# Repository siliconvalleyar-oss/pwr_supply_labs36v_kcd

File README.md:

# Fuente de Laboratorio Analógica 0-36V DC

Proyecto KiCad de una fuente de alimentación de laboratorio regulada, de 0 a 36 voltios DC, con diseño 100% analógico.

## Especificaciones

| Parámetro | Valor |
|-----------|-------|
| Salida | 0 – 36 V DC continuo |
| Corriente máxima | 5 A |
| Topología | Lineal, regulador serie |
| Control | Analógico (BJT + MOSFET) |
| Indicador | LED de potencia |
| Tensión de entrada | A definir (transformador + rectificador) |

## Estructura del Proyecto

```
pwr_supply_labs36v_kcd/
├── power_supply_36v_analog/
│   ├── power_supply_36v_analog.kicad_pro    # Archivo principal KiCad
│   ├── power_supply_36v.kicad_sch           # Esquema raíz (jerárquico)
│   ├── control_driver.kicad_sch             # Hoja: driver de control
│   ├── pwr_driver_output.kicad_sch          # Hoja: driver de potencia
│   ├── output_pwr.kicad_sch                 # Hoja: etapa de salida
│   ├── power_supply_36v_analog.kicad_pcb    # Layout de PCB
│   ├── Library_power_labs_libraries.kicad_sym  # Librería de símbolos
│   └── sym-lib-table                        # Tabla de librerías
├── helps/                                   # Datasheets, fotos, listas
├── docs/                                    # Documentación de diseño
├── .gitignore
└── README.md
```

## Hojas Jerárquicas

El esquema está dividido en 4 hojas jerárquicas:

### 1. `power_supply_36v` — Fuente principal
Etapa de entrada y regulación de tensión base.

### 2. `control_driver` — Driver de control
Circuito de control que regula la tensión de salida mediante realimentación.

### 3. `pwr_driver_output` — Driver de potencia
Etapa de amplificación de corriente con transistores de potencia (MJL21194/MJL21193).

### 4. `output_pwr` — Etapa de salida
MOSFETs de salida (5.5N45V) y diodos de protección.

## Lista de Componentes Principales

| Ref | Componente | Descripción | Uso |
|-----|------------|-------------|-----|
| Q1, Q2 | P_Q4V5N | 5.5N 45V 5A N-MOSFET | Salida de potencia |
| Q3 | P_MJL21194 | NPN 250V 16A 200W | Driver NPN |
| Q4 | P_MJL21193 | PNP 250V 16A 200W | Driver PNP |
| Q5 | P_TIP41C | NPN 100V 6A 65W | Pre-driver NPN |
| Q6 | P_TIP42C | PNP 100V 6A 65W | Pre-driver PNP |
| D1, D2 | P_BZX84C12 | Zener 12V | Regulación |
| D3 | P_1N4742 | Zener 12V 1W | Regulación |
| D4 | P_RD91ES | LED rojo | Indicador |
| D5-D7 | P_MRA4007T3G | 700V 1A Rápido | Rectificación |
| D8, D9 | P_SR560 | Schottky 60V 5A | Salida |
| R1 | P_1806 | 68K 3W | Potencia |

## Requisitos

- [KiCad 8.0](https://www.kicad.org/) o superior
- macOS / Linux / Windows

## Abrir el Proyecto

```bash
# Clonar repositorio
git clone https://github.com/TU_USUARIO/pwr_supply_labs36v_kcd.git
cd pwr_supply_labs36v_kcd

# Abrir en KiCad
open power_supply_36v_analog/power_supply_36v_analog.kicad_pro
```

## Diseño Jerárquico

```
┌─────────────────────────────────────────────────────┐
│              power_supply_36v.kicad_sch              │
│                                                     │
│  ┌──────────────┐    ┌──────────────┐              │
│  │ control_     │    │ pwr_driver_  │              │
│  │ driver       │────│ output       │──── Salida   │
│  └──────────────┘    └──────────────┘              │
│         │                                          │
│  ┌──────────────┐                                  │
│  │ output_pwr   │                                  │
│  └──────────────┘                                  │
└─────────────────────────────────────────────────────┘
```

## Licencia

Este proyecto utiliza KiCad, que está bajo licencia **GPL v2+**. Los archivos fuente de este proyecto son compatibles con esta licencia.

## Autor

**ERTS DIGITAL**

---

*Proyecto de fuente de laboratorio analógica de alta potencia para uso educativo y de laboratorio.*

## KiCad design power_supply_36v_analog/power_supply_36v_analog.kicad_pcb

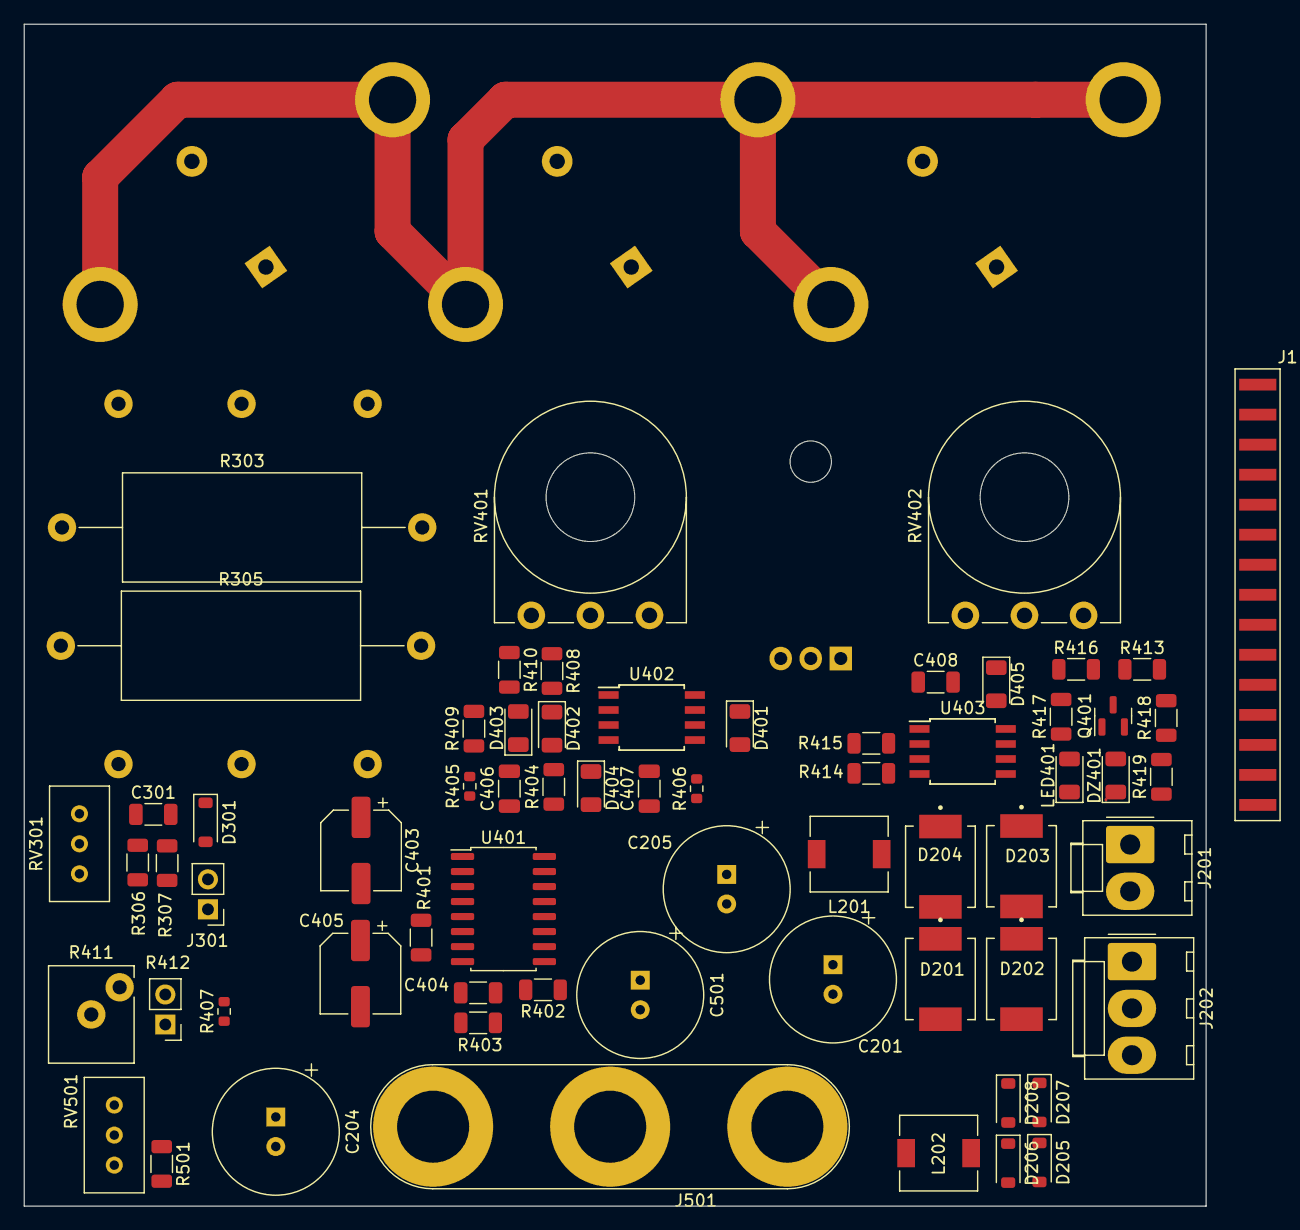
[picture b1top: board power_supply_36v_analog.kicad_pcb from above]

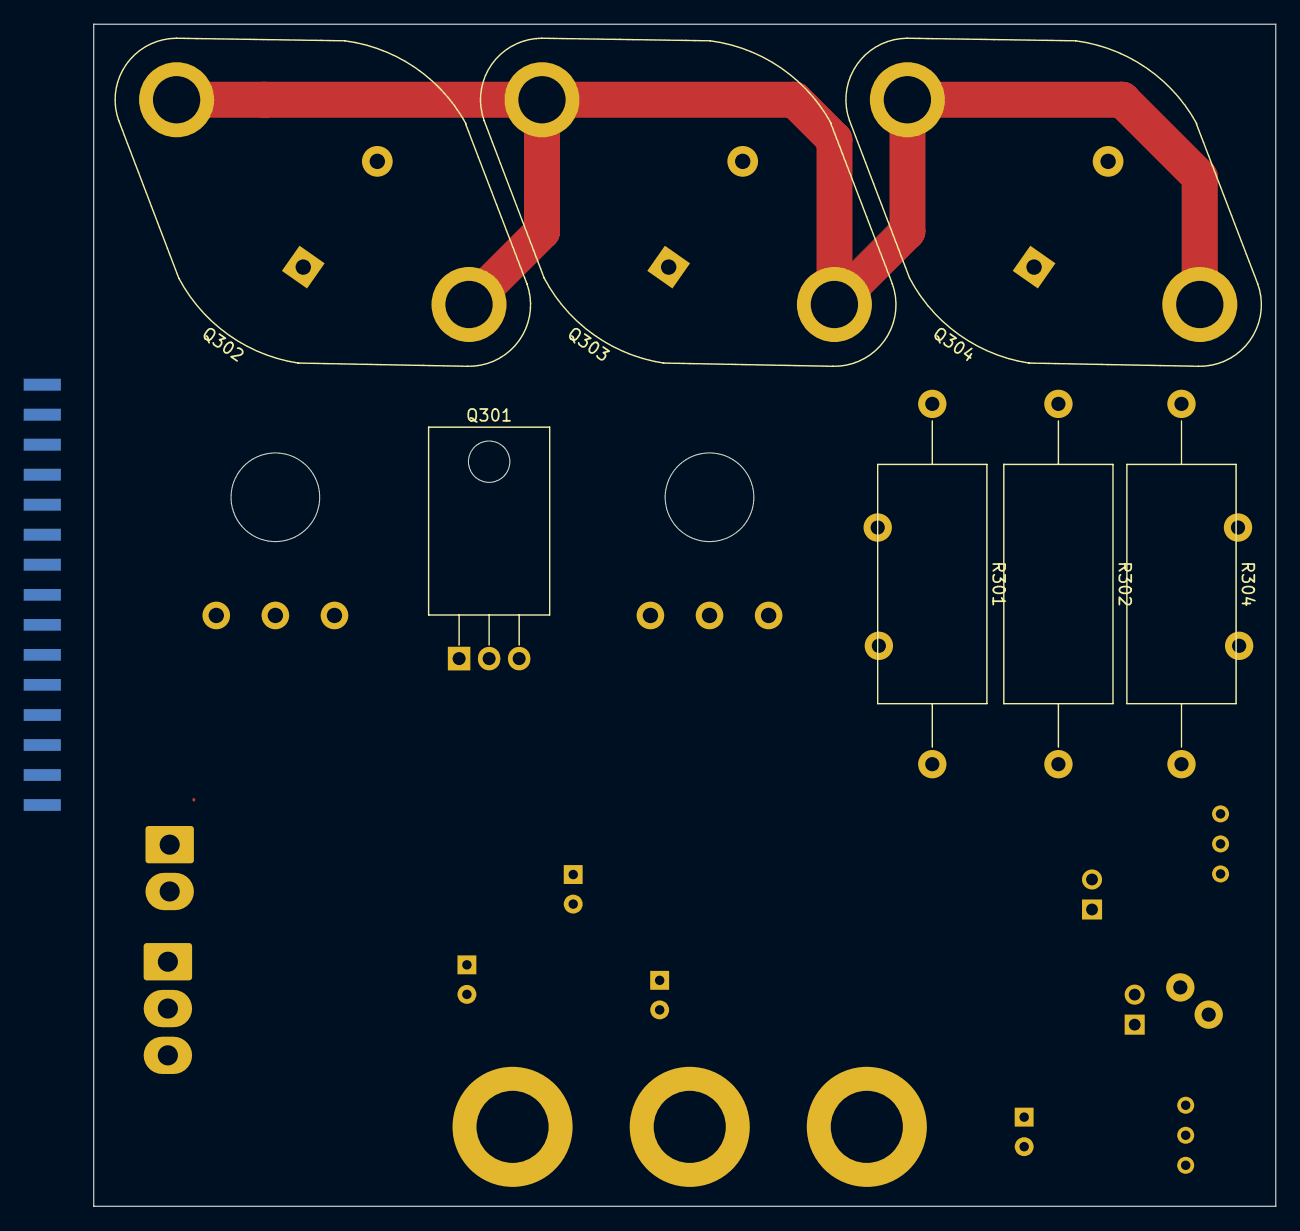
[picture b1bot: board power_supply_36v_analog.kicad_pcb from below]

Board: 2 copper layers, 100.0 x 100.0 mm, 73 parts (7 on the bottom side), 45 nets.

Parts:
C201: 4700ufx63v; CP_Radial_Tantal_D10.5mm_P2.50mm
C204, C205: 1000ufx25v; CP_Radial_Tantal_D10.5mm_P2.50mm
C301: 820nf; C_1206_3216Metric
C403: 100uf 10V; CP_Elec_6.3x5.4
C404, C407: 100pf; C_1206_3216Metric
C405: 10ufx25v; CP_Elec_6.3x5.4
C406: 1nf; C_1206_3216Metric
C408: 56pf; C_1206_3216Metric
C501: 47uf x 63v; CP_Radial_Tantal_D10.5mm_P2.50mm
D201, D202, D203, D204: 1N4007 50V 3Amp; DIO_SS34
D205, D206, D207, D208, D301: 1N4001; D_SOD-123
D401, D402, D403, D404, D405: 1N4148; D_1206_3216Metric
DZ401: Zener 3v3 400mv; D_1206_3216Metric
J1: Conn_02x15_Odd_Even; PinHeader_2x15_P2.54mm_Vertical_edge_mount_smd
J201: Transformador 36 volt AC; Molex_KK-396_A-41791-0002_1x02_P3.96mm_Vertical
J202: Transformador 15 + 15 volt AC; Molex_KK-396_A-41791-0003_1x03_P3.96mm_Vertical
J301: JUMPER_0.22; PinHeader_1x02_P2.54mm_Vertical
J501: OUTPUT; Banana_Jack_3Pin
L201, L202: 100mh; L_6.3x6.3_H3
LED401: RED; LED_1206_3216Metric
Q301: BD241; TO-220-3_Horizontal_TabDown
Q302, Q303, Q304: 2N3055; TO-3
Q401: BC559C; SOT-23
R301, R302, R304: 0r22 1W; R_Axial_DIN0922_L20.0mm_D9.0mm_P30.48mm_Horizontal
R303: 10r 1W; R_Axial_DIN0922_L20.0mm_D9.0mm_P30.48mm_Horizontal
R305: 0.22 4W; R_Axial_DIN0922_L20.0mm_D9.0mm_P30.48mm_Horizontal
R306: 5k6; R_1206_3216Metric
R307: 46; R_1206_3216Metric
R401, R402, R409, R414, R415, R419: 4k7; R_1206_3216Metric
R403: 22; R_1206_3216Metric
R404: 2k2; R_1206_3216Metric
R405: 1k; R_0603_1608Metric
R406: 4k7; R_0603_1608Metric
R407: 10k; R_0603_1608Metric
R408: 10M; R_1206_3216Metric
R410, R417: 10k; R_1206_3216Metric
R411: 4k7 1W; R_Radial_Power_L7.0mm_W8.0mm_Px2.40mm_Py2.30mm
R412: 0.22 4W JUMPER; PinHeader_1x02_P2.54mm_Vertical
R413, R416: 15k; R_1206_3216Metric
R418: 1k; R_1206_3216Metric
R501: 270k; R_1206_3216Metric
RV301: 2k5; Potentiometer_Bourns_3296W_Vertical
RV401: P1 50K; Potentiometer_Piher_T-16L_Single_Vertical_Hole
RV402: 1K reference; Potentiometer_Piher_T-16L_Single_Vertical_Hole
RV501: 250K; Potentiometer_Bourns_3296W_Vertical
U401: LM723; SO-16_5.3x10.2mm_P1.27mm
U402, U403: LM741; SOIC-8W_5.3x5.3mm_P1.27mm

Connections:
+15V: C204.1, D401.1 (K), L202.2, Q401.3 (E), R418.2, U401.11 (VC), U401.12 (V+), U402.7 (V+), U403.7 (V+)
+36V: C201.1, D301.1 (K), L201.2, Q301.2 (C), Q302.3 (C), Q303.3 (C), Q304.3 (C)
-15V: C205.2, D205.2 (A), D206.2 (A), RV402.2, U402.4 (V-), U403.4 (V-)
-36V: C201.2, D201.2 (A), D202.2 (A)
/control_driver/p11: R408.1, R409.2, R410.1, RV401.3
/openScopeDigilentAnalogDevices/GND: J1.19, J1.20, J1.25, J1.26
AMPERIMETRO+: RV301.2, RV301.3
GND: C204.2, C205.1, C301.2, C403.2, C405.2, J202.2, J501.1, LED401.1 (K), R307.1, R406.1, U401.7 (V-)
NODO_001: D301.2 (A), J301.1, R301.2, R302.2, R303.2, R304.2, R305.1, R306.1, R411.2, R415.1
unnamed: C406.1, R405.2
unnamed: D203.1 (K), D204.1 (K), L201.1
unnamed: D207.1 (K), D208.1 (K), L202.1
unnamed: C405.1, D401.2 (A), R402.1, R404.1, R408.2, R410.2, R413.2, R416.2, U401.3 (CSEN)
unnamed: C406.2, D402.2 (A), D403.1 (K), R409.1, U402.3 (+)
unnamed: C407.1, D402.1 (K), D403.2 (A), R406.2, U402.2 (-)
unnamed: C407.2, D404.1 (K), U402.6
unnamed: C408.2, D405.1 (K), R419.1, U403.6
unnamed: DZ401.2 (A), R419.2
unnamed: DZ401.1 (K), Q401.2 (B), R418.1
unnamed: LED401.2 (A), R417.1
unnamed: Q301.3 (E), Q302.1 (B), Q303.1 (B), Q304.1 (B), R303.1
unnamed: Q302.2 (E), R301.1
unnamed: Q303.2 (E), R302.1
unnamed: Q304.2 (E), R304.1
unnamed: Q401.1 (C), R417.2
unnamed: R306.2, RV301.1
unnamed: R413.1, R416.1, RV402.1
unnamed: R414.1, RV402.3
unnamed: R501.2, RV501.1, RV501.2
unnamed: C403.1, R401.1, U401.5 (+)
unnamed: C404.2, R402.2, R403.1, U401.4 (-)
unnamed: C404.1, U401.13 (FC)
unnamed: R403.2, U401.2 (ILIM), U401.10 (Vout)
unnamed: R401.2, U401.6 (VREF)
unnamed: R414.2, U403.3 (+)
unnamed: C408.1, R415.2, U403.2 (-)
TR11: D205.1 (K), D207.2 (A), J202.3
TR12: D206.1 (K), D208.2 (A), J202.1
TR21: D201.1 (K), D204.2 (A), J201.2
TR22: D202.1 (K), D203.2 (A), J201.1
U+: C301.1, C501.1, J301.2, J501.2, R305.2, R307.2
U-: C501.2, R407.1, R411.1, R412.1, R501.1
US-: R405.1, R407.2, RV401.1, RV401.2
output_U-: J501.3, R412.2
to_base_driver_adjust: D404.2 (A), D405.2 (A), Q301.1 (B), R404.2
